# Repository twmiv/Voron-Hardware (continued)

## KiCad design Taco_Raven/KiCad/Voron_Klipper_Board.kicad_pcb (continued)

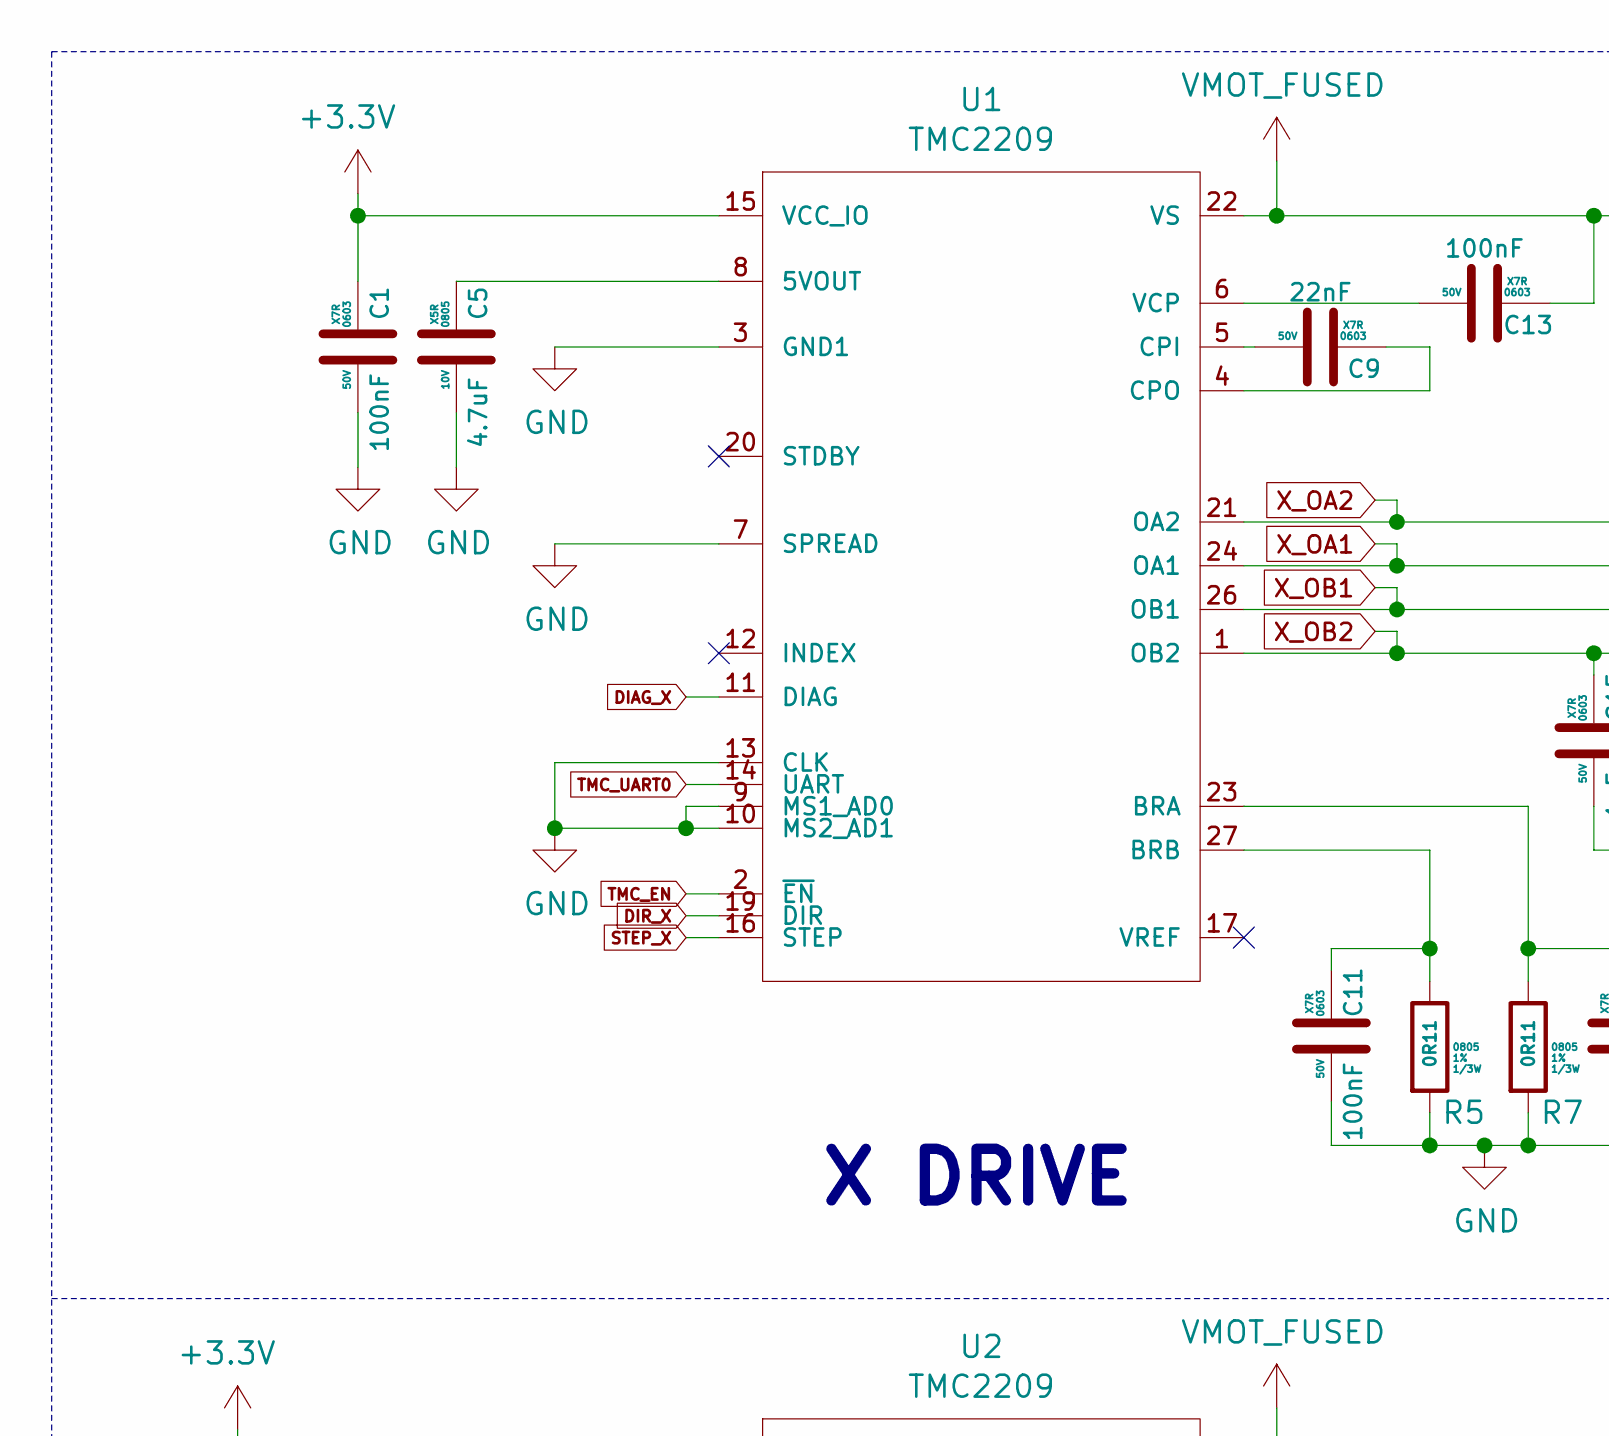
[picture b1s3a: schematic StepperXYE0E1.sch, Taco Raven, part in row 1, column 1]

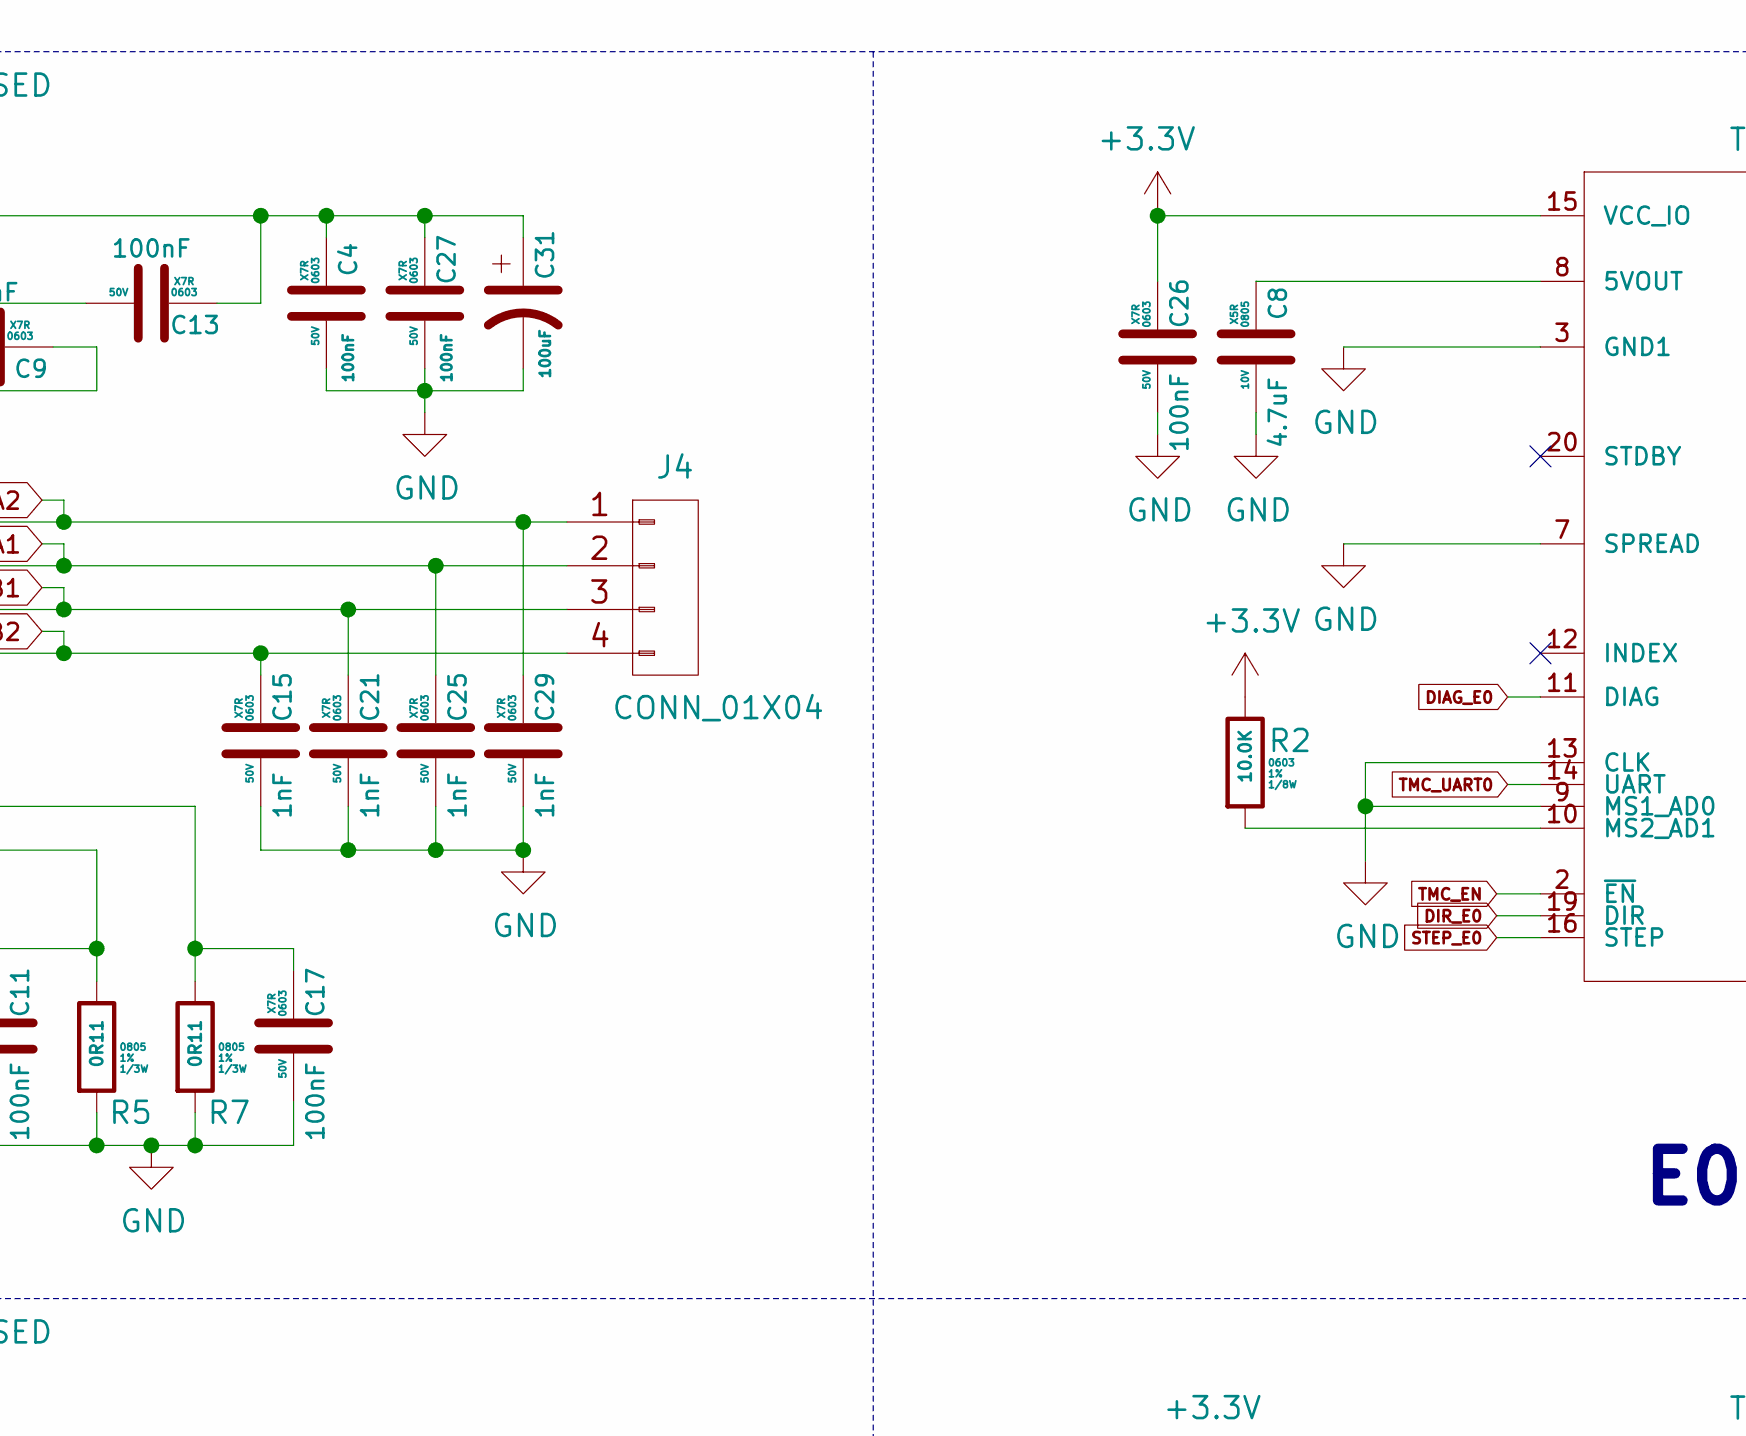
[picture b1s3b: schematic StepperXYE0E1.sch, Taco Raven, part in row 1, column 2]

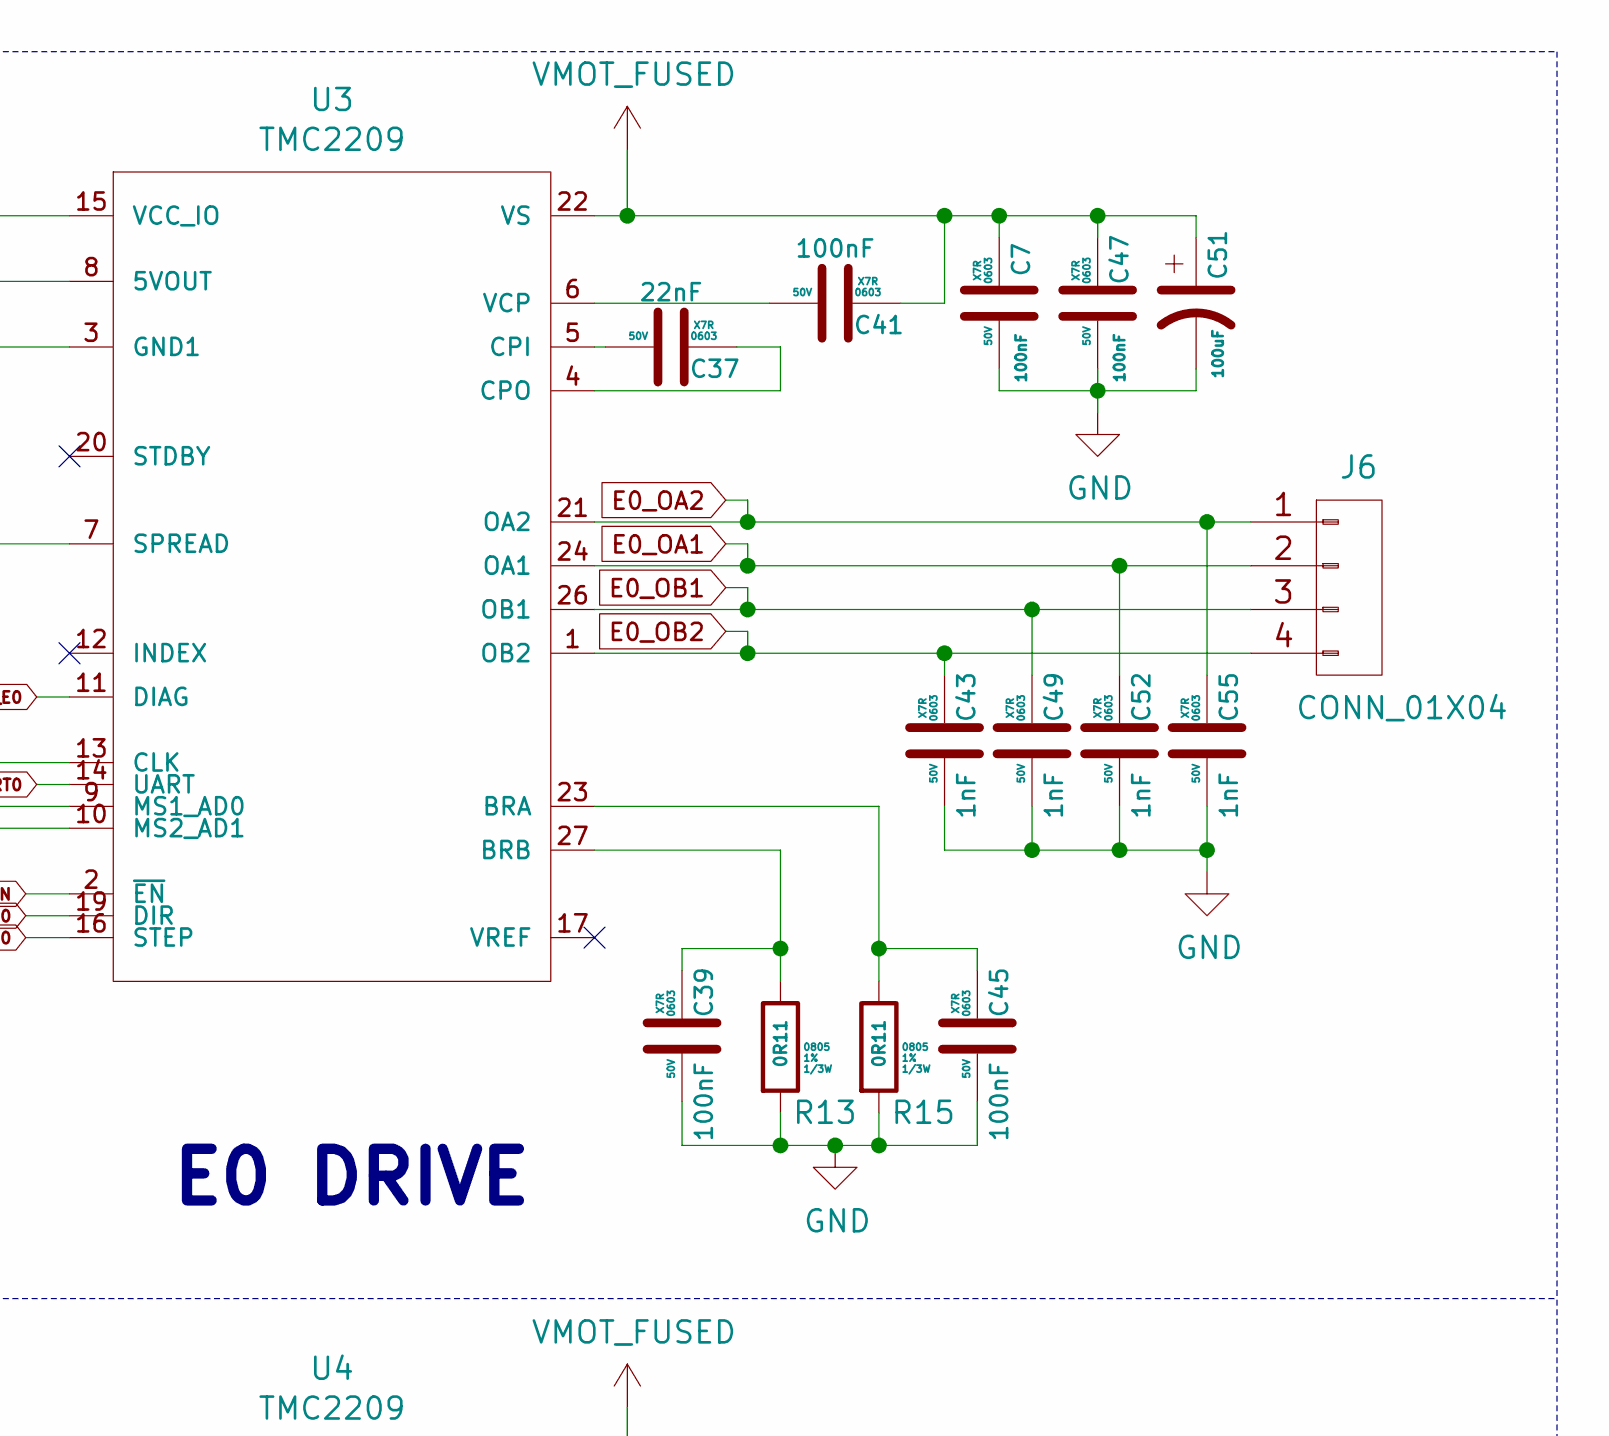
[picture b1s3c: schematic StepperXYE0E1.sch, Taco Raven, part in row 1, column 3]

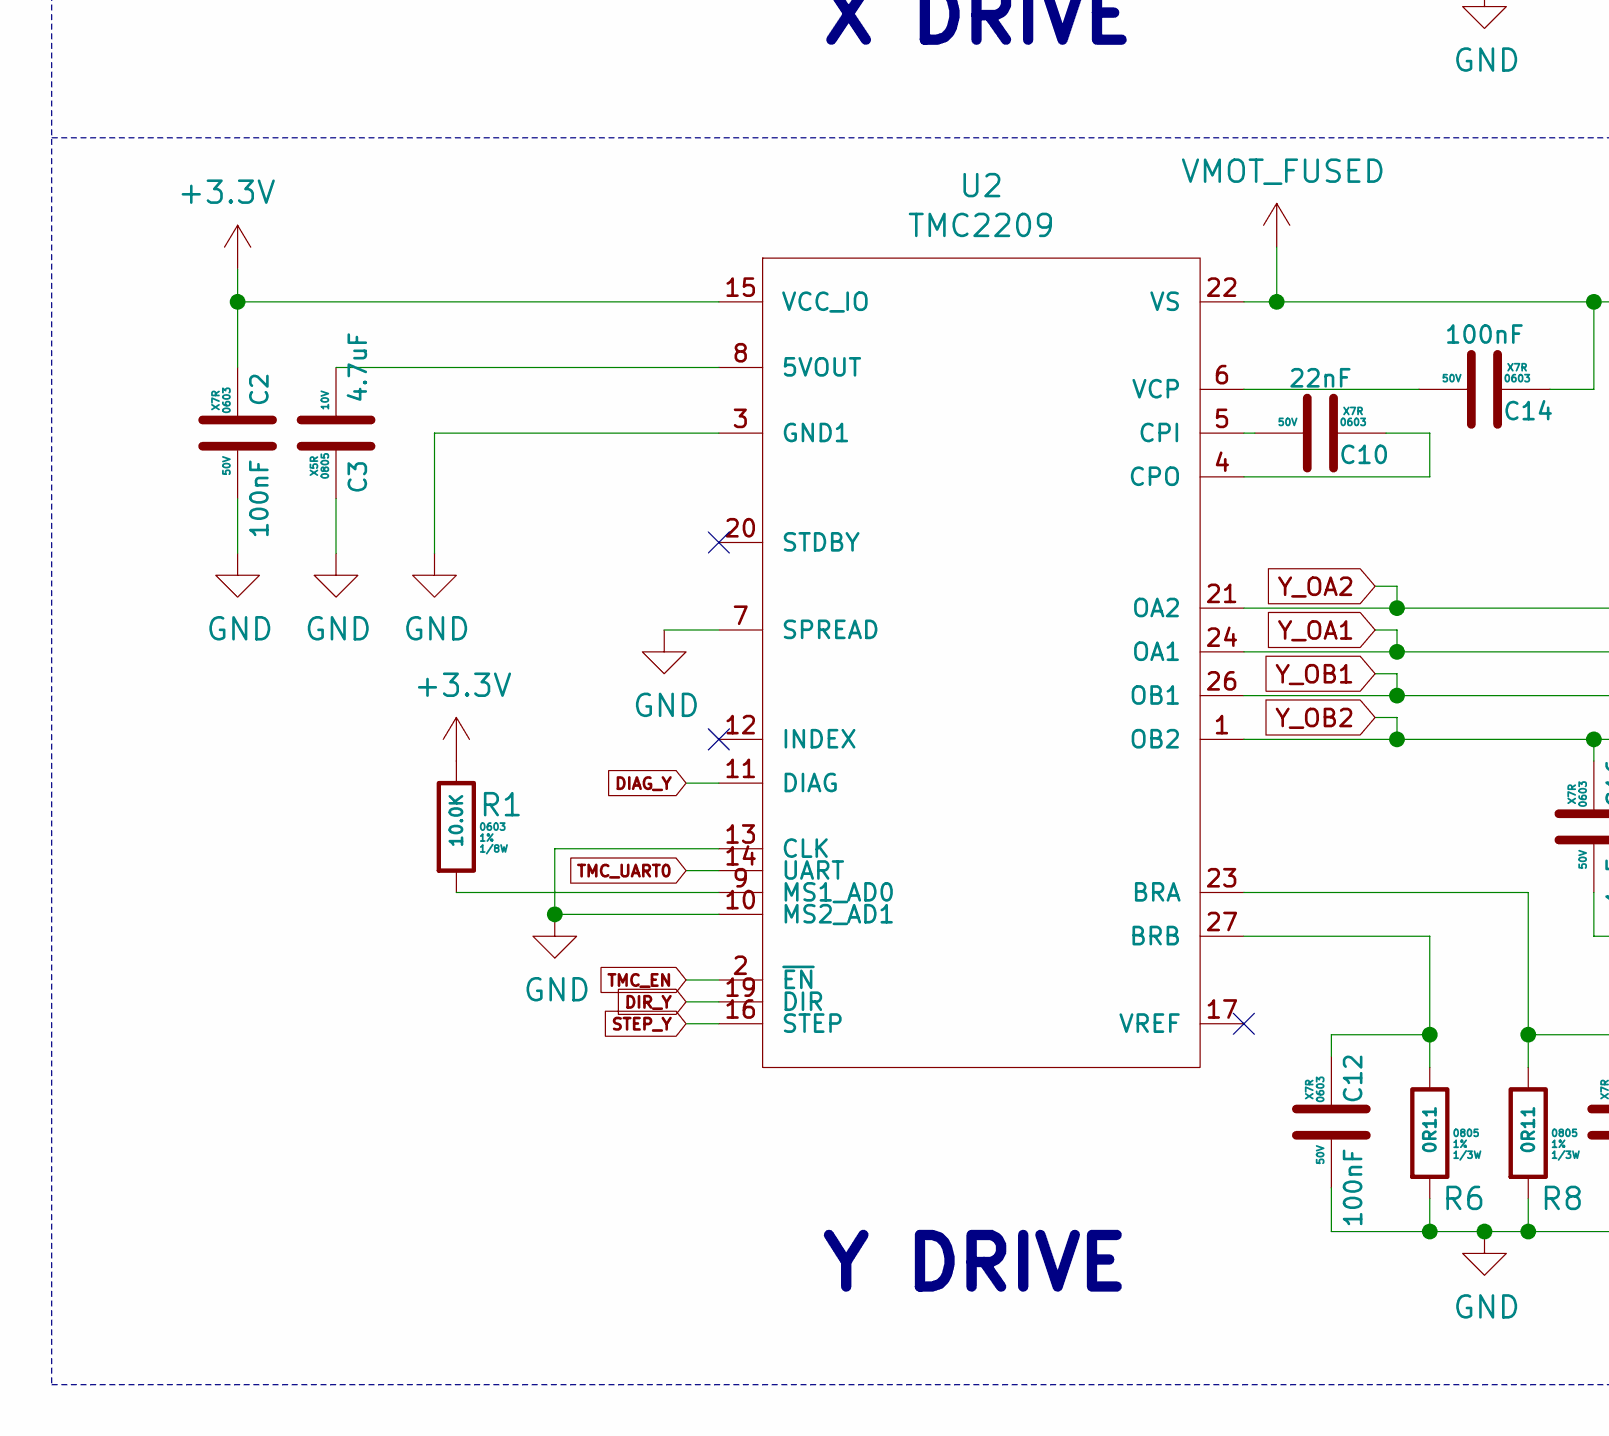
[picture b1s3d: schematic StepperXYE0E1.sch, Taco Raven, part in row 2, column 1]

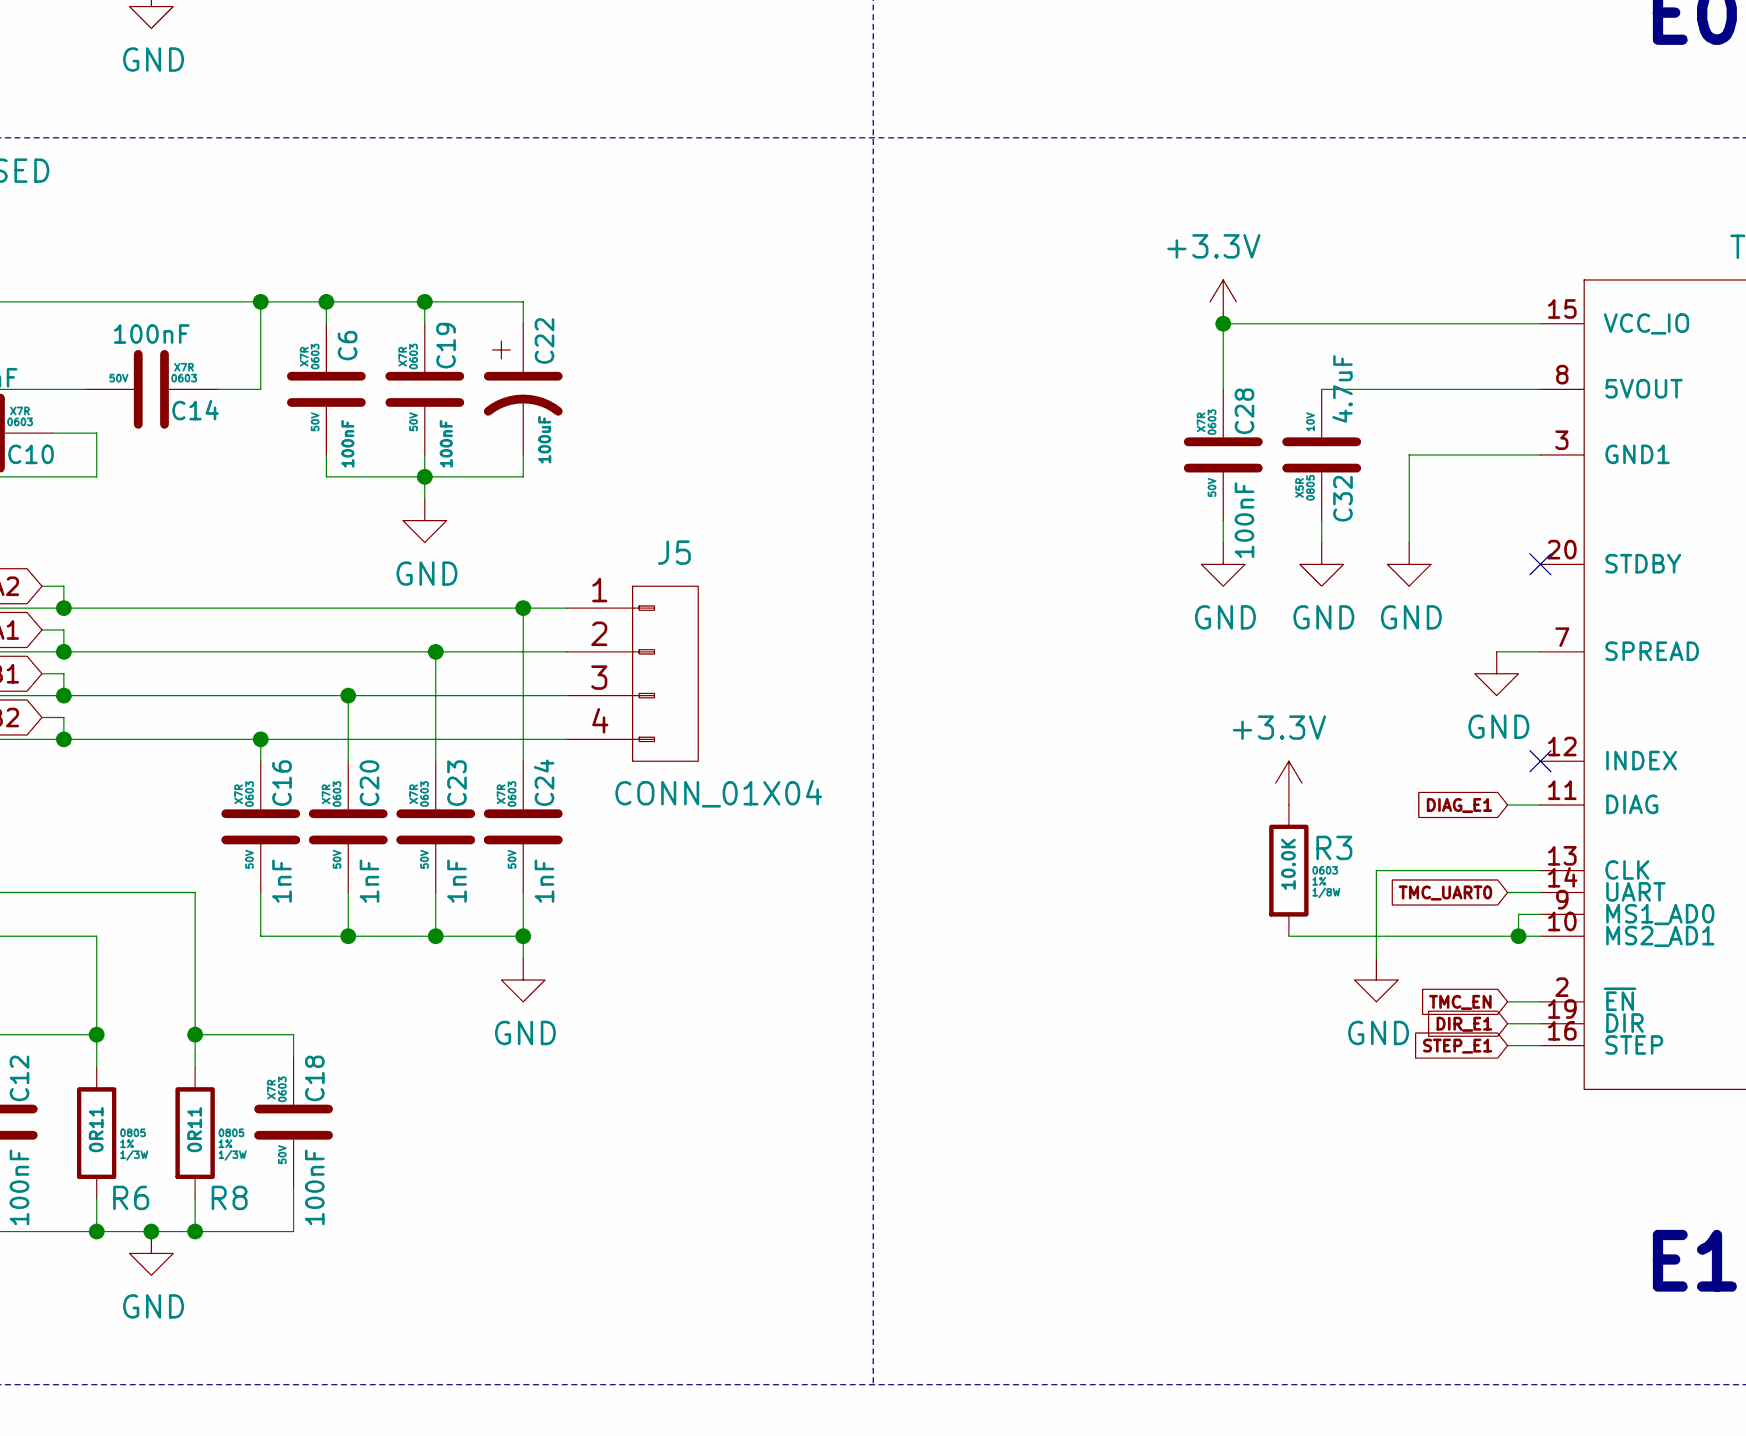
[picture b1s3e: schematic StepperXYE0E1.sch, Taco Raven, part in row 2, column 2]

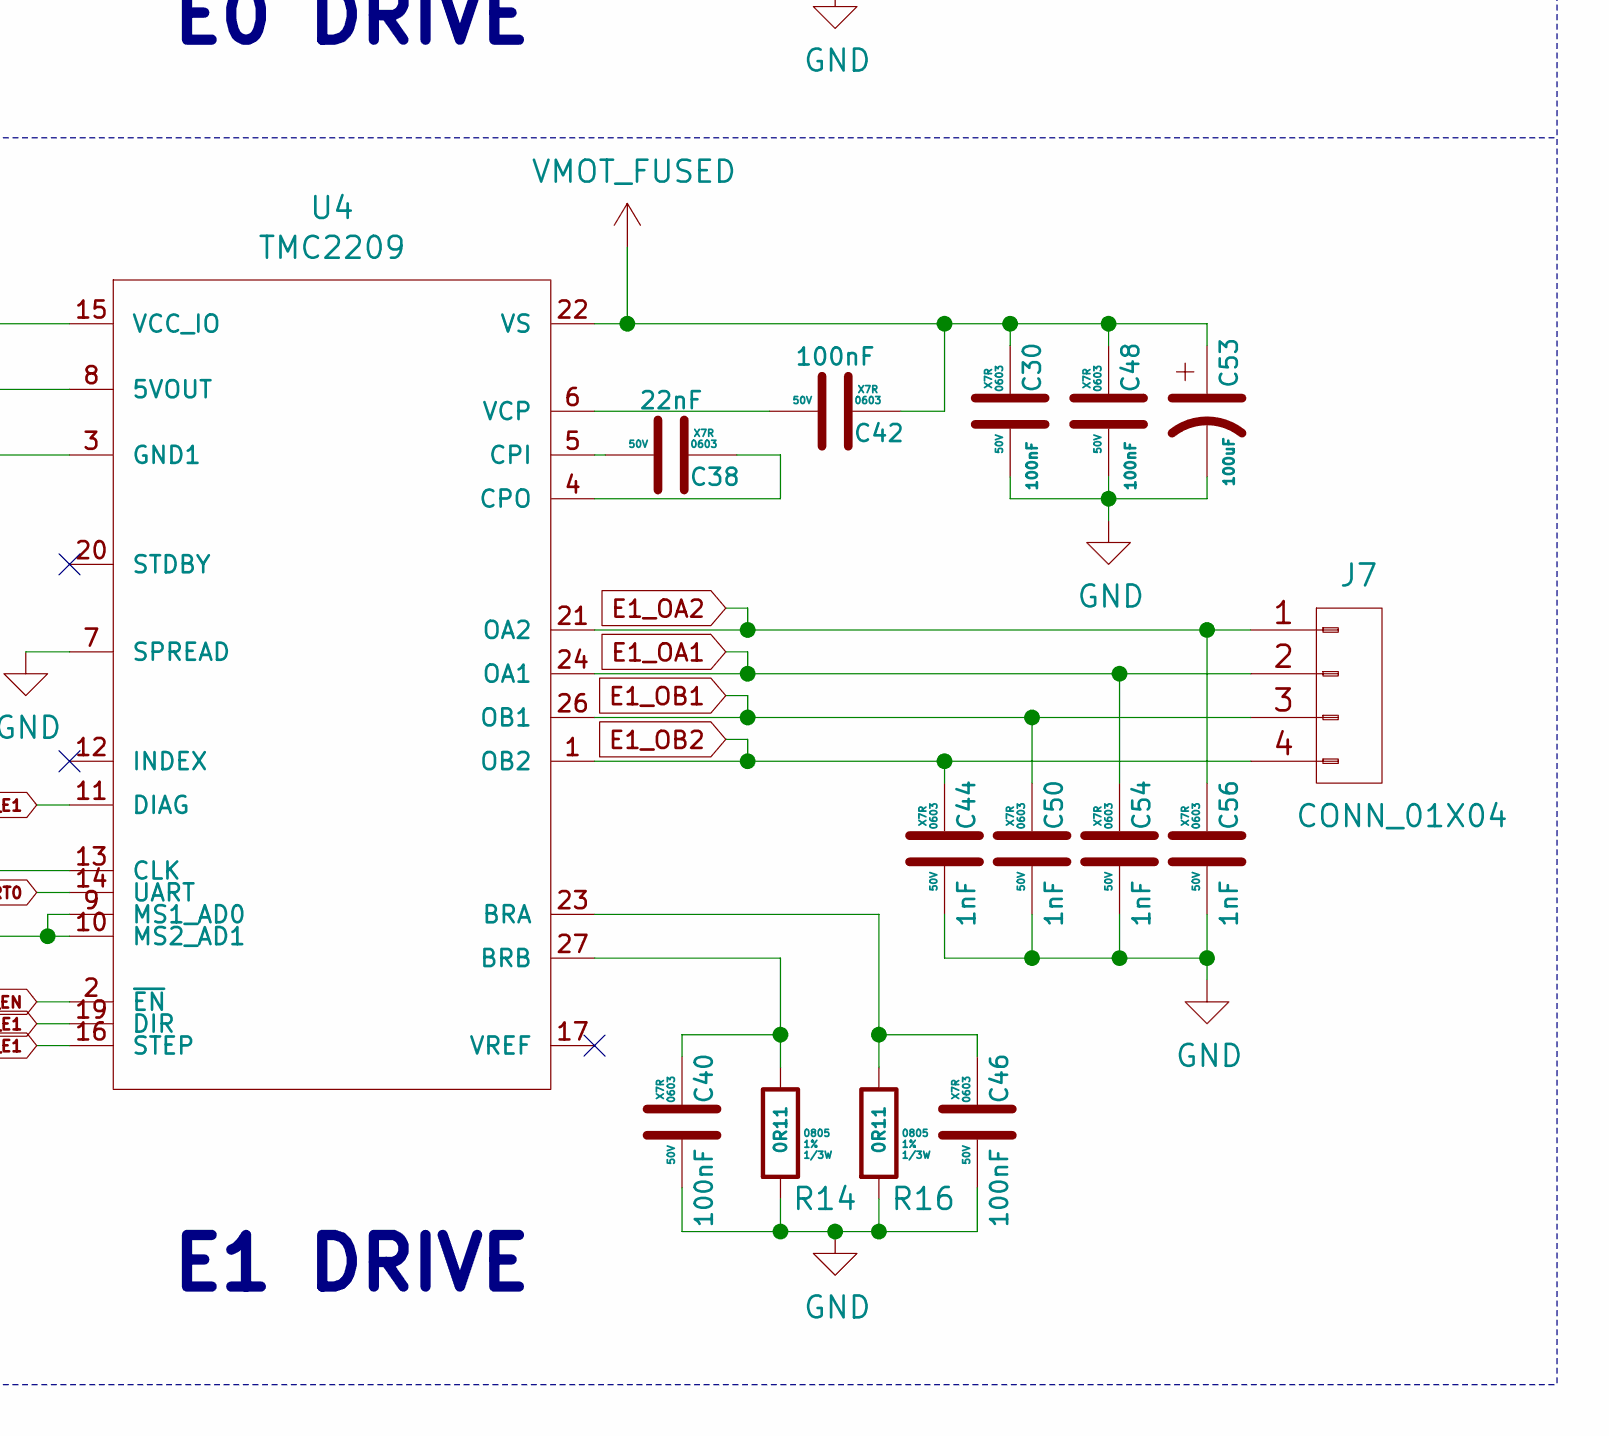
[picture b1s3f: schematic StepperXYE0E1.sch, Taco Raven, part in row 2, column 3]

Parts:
C1, C2, C4, C6, C7, C11, C12, C13, C14, C17, C18, C19, C26, C27, C28, C30, C39, C40, C41, C42, C45, C46, C47, C48: 100nF; C_0603; Voltage 50V; MFG PN CC0603KRX7R9BB104; Digikey P/N 311-1344-1-ND
C3, C5, C8, C32: 4.7uF; C_0805; Voltage 10V; MFG PN CL21A475KPFNNNG; Digikey P/N 1276-6464-1-ND
C9, C10, C37, C38: 22nF; C_0603; Voltage 50V; MFG PN CL10B223KB8WPNC; Digikey P/N 311-3601-1-ND
C15, C16, C20, C21, C23, C24, C25, C29, C43, C44, C49, C50, C52, C54, C55, C56: 1nF; C_0603; Voltage 50V; MFG PN CC0603KRX7R9BB102; Digikey P/N 311-1080-1-ND
C22, C31, C51, C53: 100uF; CP_Elec_6.3x7.7; Voltage 50V; MFG PN EMZR500ARA101MF80G; Digikey P/N 565-5153-1-ND
J4, J5, J6, J7: CONN_01X04; Molex_KK_1X4; MFG PN 0022232041; Digikey P/N WM4202-ND
R1, R2, R3: 10.0K; R_0603; Tolerance 1%; MFG PN RNCP0603FTD10K0; Digikey P/N RNCP0603FTD10K0CT-ND
R5, R6, R7, R8, R13, R14, R15, R16: 0R11; R_0805; Tolerance 1%; MFG PN RL1220S-R11-F; Digikey P/N RL12S.11FCT-ND
U1, U2, U3, U4: TMC2209; QFN-28_EP_5x5_Pitch0.5mm

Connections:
+3.3V: C1.2, C2.2, C26.2, C28.2, R1.1, R2.1, R3.1, U1.15 (VCC_IO), U2.15 (VCC_IO), U3.15 (VCC_IO), U4.15 (VCC_IO); also elsewhere on the board
DIAG_E0: U3.11 (DIAG); also elsewhere on the board
DIAG_E1: U4.11 (DIAG); also elsewhere on the board
DIAG_X: U1.11 (DIAG); also elsewhere on the board
DIAG_Y: U2.11 (DIAG); also elsewhere on the board
DIR_E0: U3.19 (DIR); also elsewhere on the board
DIR_E1: U4.19 (DIR); also elsewhere on the board
DIR_X: U1.19 (DIR); also elsewhere on the board
DIR_Y: U2.19 (DIR); also elsewhere on the board
E0_OA1: C52.2, J6.2, U3.24 (OA1)
E0_OA2: C55.2, J6.1, U3.21 (OA2)
E0_OB1: C49.2, J6.3, U3.26 (OB1)
E0_OB2: C43.2, J6.4, U3.1 (OB2)
E1_OA1: C54.2, J7.2, U4.24 (OA1)
E1_OA2: C56.2, J7.1, U4.21 (OA2)
E1_OB1: C50.2, J7.3, U4.26 (OB1)
E1_OB2: C44.2, J7.4, U4.1 (OB2)
GND: C1.1, C2.1, C3.2, C4.1, C5.1, C6.1, C7.1, C8.1, C11.1, C12.1, C15.1, C16.1, C17.1, C18.1, C19.1, C20.1, C21.1, C22.2, C23.1, C24.1, C25.1, C26.1, C27.1, C28.1, C29.1, C30.1, C31.2, C32.2, C39.1, C40.1, C43.1, C44.1, C45.1, C46.1, C47.1, C48.1, C49.1, C50.1, C51.2, C52.1, C53.2, C54.1, C55.1, C56.1, R5.2, R6.2, R7.2, R8.2, R13.2, R14.2, R15.2, R16.2, U1.3 (GND1), U1.7 (SPREAD), U1.9 (MS1_AD0), U1.10 (MS2_AD1), U1.13 (CLK), U1.18 (GND2), U1.25 (GND3), U1.29 (G_PAD), U2.3 (GND1), U2.7 (SPREAD), U2.10 (MS2_AD1), U2.13 (CLK), U2.18 (GND2), U2.25 (GND3), U2.29 (G_PAD), U3.3 (GND1), U3.7 (SPREAD), U3.9 (MS1_AD0), U3.13 (CLK), U3.18 (GND2), U3.25 (GND3), U3.29 (G_PAD), U4.3 (GND1), U4.7 (SPREAD), U4.13 (CLK), U4.18 (GND2), U4.25 (GND3), U4.29 (G_PAD); also elsewhere on the board
unnamed: C3.1, U2.8 (5VOUT)
unnamed: C5.2, U1.8 (5VOUT)
unnamed: C8.2, U3.8 (5VOUT)
unnamed: C9.1, U1.5 (CPI)
unnamed: C9.2, U1.4 (CPO)
unnamed: C10.1, U2.5 (CPI)
unnamed: C10.2, U2.4 (CPO)
unnamed: C11.2, R5.1, U1.27 (BRB)
unnamed: C12.2, R6.1, U2.27 (BRB)
unnamed: C13.1, U1.6 (VCP)
unnamed: C14.1, U2.6 (VCP)
unnamed: C17.2, R7.1, U1.23 (BRA)
unnamed: C18.2, R8.1, U2.23 (BRA)
unnamed: C32.1, U4.8 (5VOUT)
unnamed: C37.1, U3.5 (CPI)
unnamed: C37.2, U3.4 (CPO)
unnamed: C38.1, U4.5 (CPI)
unnamed: C38.2, U4.4 (CPO)
unnamed: C39.2, R13.1, U3.27 (BRB)
unnamed: C40.2, R14.1, U4.27 (BRB)
unnamed: C41.1, U3.6 (VCP)
unnamed: C42.1, U4.6 (VCP)
unnamed: C45.2, R15.1, U3.23 (BRA)
unnamed: C46.2, R16.1, U4.23 (BRA)
unnamed: R1.2, U2.9 (MS1_AD0)
unnamed: R2.2, U3.10 (MS2_AD1)
unnamed: R3.2, U4.9 (MS1_AD0), U4.10 (MS2_AD1)
STEP_E0: U3.16 (STEP); also elsewhere on the board
STEP_E1: U4.16 (STEP); also elsewhere on the board
STEP_X: U1.16 (STEP); also elsewhere on the board
STEP_Y: U2.16 (STEP); also elsewhere on the board
TMC_EN: U1.2 (~EN), U2.2 (~EN), U3.2 (~EN), U4.2 (~EN); also elsewhere on the board
TMC_UART0: U1.14 (UART), U2.14 (UART), U3.14 (UART), U4.14 (UART); also elsewhere on the board
VMOT_FUSED: C4.2, C6.2, C7.2, C13.2, C14.2, C19.2, C22.1, C27.2, C30.2, C31.1, C41.2, C42.2, C47.2, C48.2, C51.1, C53.1, U1.22 (VS), U1.28 (VS), U2.22 (VS), U2.28 (VS), U3.22 (VS), U3.28 (VS), U4.22 (VS), U4.28 (VS); also elsewhere on the board
X_OA1: C25.2, J4.2, U1.24 (OA1)
X_OA2: C29.2, J4.1, U1.21 (OA2)
X_OB1: C21.2, J4.3, U1.26 (OB1)
X_OB2: C15.2, J4.4, U1.1 (OB2)
Y_OA1: C23.2, J5.2, U2.24 (OA1)
Y_OA2: C24.2, J5.1, U2.21 (OA2)
Y_OB1: C20.2, J5.3, U2.26 (OB1)
Y_OB2: C16.2, J5.4, U2.1 (OB2)

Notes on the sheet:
X DRIVE
Y DRIVE
E0 DRIVE
E1 DRIVE
